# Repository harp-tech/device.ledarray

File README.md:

## Harp LED array

Controlling LED arrays that require more power. Ideally for opto-stimulation experiments.

### Key Features ###

* Controls up to 2 separate RGB LED
* Arrays and one common Infrared LED
* Two operation modes for each RGB LED Array: PWM or Interval

### Connectivity ###

* 1x clock sync input (CLKIN) [stereo jack]
* 1x USB (for computer) [USB type B]
* 1x flat cable
* 2x Digital Inputs (IN0, IN1) [flick lock male pins]
* 2x Digital Outputs (OUT0, OUT1) [flick lock male pins]
* 1x connector for 2 LED Arrays [10-pin flat-cable]

## Interface ##

The interface with the Harp board can be done through [Bonsai](https://bonsai-rx.org/) or a dedicated GUI (Graphical User Interface).

In order to use this GUI, there are some software that needs to be installed:

1 - Install the [drivers](https://bitbucket.org/fchampalimaud/downloads/downloads/UsbDriver-2.12.26.zip).

2 - Install the [runtime](https://bitbucket.org/fchampalimaud/downloads/downloads/Runtime-1.0.zip).

3 - Reboot the computer.

4 - Install the [GUI](https://bitbucket.org/fchampalimaud/downloads/downloads/Harp%20Led%20Array%20v2.2.0.zip).

## Licensing ##

Each subdirectory will contain a license or, possibly, a set of licenses if it involves both hardware and software.

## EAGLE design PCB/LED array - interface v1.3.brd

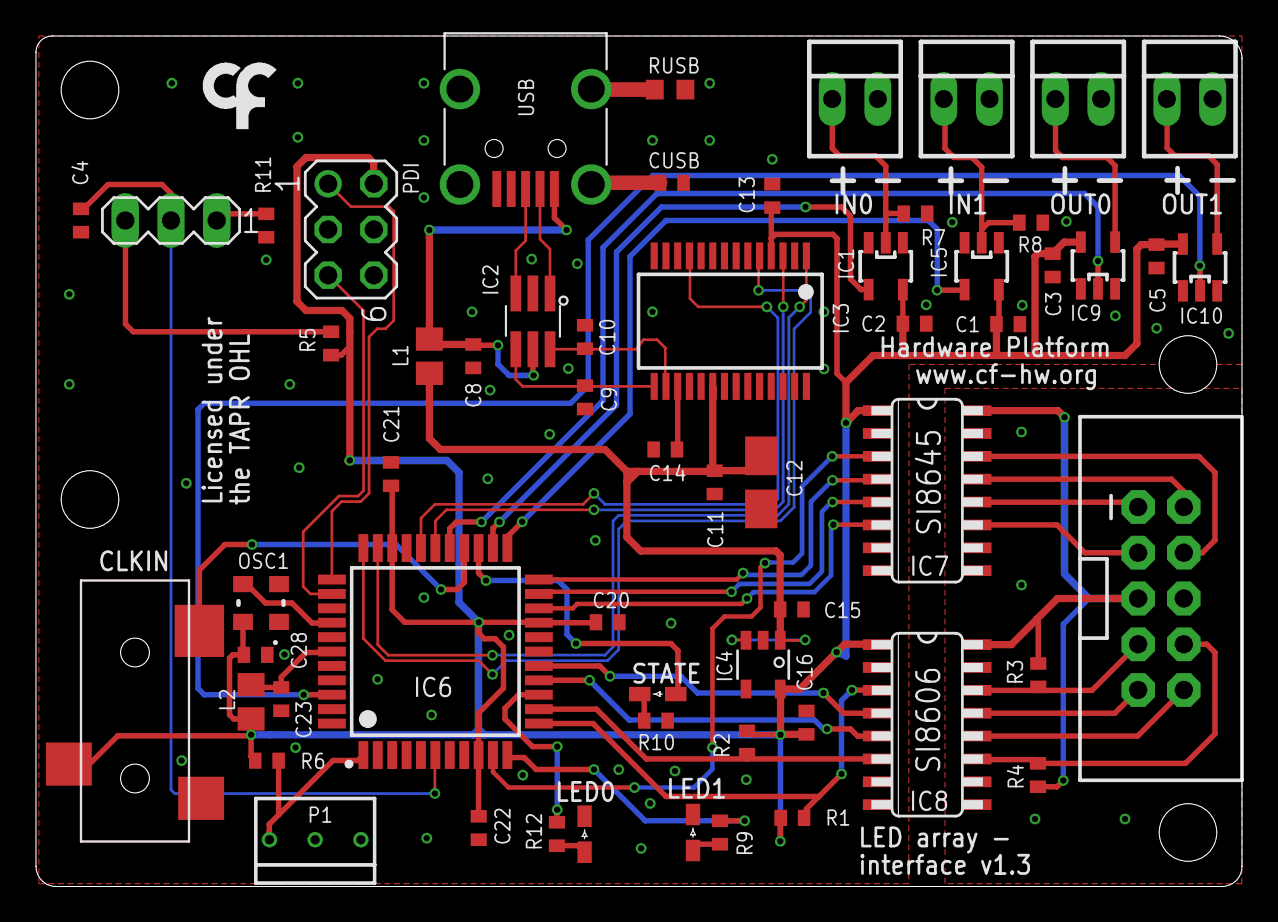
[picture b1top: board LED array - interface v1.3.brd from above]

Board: 2 copper layers, 67.0 x 47.2 mm, 61 parts (1 on the bottom side), 56 nets.

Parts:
C1, C2, C3, C5, C8, C11, C13, C14, C20, C21, C22, C28: 100nF; C0402
C4: 330nF NA; C0402
C9, C10: 47pF; C0402
C12: 4.7uF; A/3216-18W
C15, C16: 4.7uF; C0402
C23: 330nF; C0402
CLKIN: 35RASMT2BHNTRX
CUSB: 4.7nF; C0402
IC1, IC5, IC9, IC10: SN74LVC1G125; SOT23-5
IC2: USBLC6-2SC6; SOT23-6L
IC3: FT232RL; SSOP28
IC4: LP5907; TSOT23-5
IC6: ATXMEGAxxxA4U-AU; QFP80P1200X1200X120-44N
IC7: SI8645; NSOIC-16
IC8: SI8606; NSOIC-16
IN0, IN1: 22-23-2021
JP1: M05X2SHD; 2X5-SHROUDED
L1: ???; R0805
L2: 1u; R0805
LED0, LED1: GREEN; LED_HAND
OSC1: OSCILLATOR_3.2X2.5
OUT0, OUT1: 22-23-2021
P1: POT_BOURNS_3362M
PDI: MA03-2
R1, R2, R3, R4: 3k; R0402
R5, R11: 100k NA; R0402
R6: 1k 0.1%; R0402
R7, R8: 100k; R0402
R9, R10, R12: 68; R0402
RUSB: 1M; R0603
STATE: GREEN; LED_HAND
SV1: NA; MA03-1
U$1: LOGO_5
U$3: LOGO_7
USB: 240-0002-1

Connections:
ADC: IC6.1, P1.3, R6.1
ADC1: R5.1, SV1.3
AUX0: IC6.22, IC7.4
AUX1: IC6.21, IC7.5
AVCC: C23.1, IC6.39, L2.1
CLK: IC8.11, JP1.8, R4.1
CLK_SYNC: CLKIN.4, IC6.26
DAT: IC8.14, JP1.7, R3.1
DO2: IC7.13, JP1.2
DO3: IC7.12, JP1.1
FT_CTS: IC3.11, IC6.29
FT_RTS: IC3.3, IC6.28
FT_RXD: IC3.5, IC6.33
FT_TXD: IC3.1, IC6.32
GND: IC7.9, IC7.15, IC8.9, JP1.6
GND2: IC5.2, IN1.1, R8.2
GNDIO: C1.2, C2.2, C3.2, C4.2, C5.2, C8.2, C9.2, C10.2, C11.2, C12.-, C13.2, C14.2, C15.1, C16.1, C20.2, C21.2, C22.2, C23.2, C28.2, CLKIN.5, CUSB.2, IC1.1, IC1.3, IC2.P$2, IC3.7, IC3.18, IC3.21, IC3.25, IC3.26, IC4.2, IC5.1, IC5.3, IC6.8, IC6.18, IC6.30, IC6.38, IC6.40, IC6.43, IC7.2, IC7.8, IC8.8, IC9.1, IC9.3, IC10.1, IC10.3, IN0.2, IN1.2, LED0.K, LED1.K, OSC1.P$2, OUT0.2, OUT1.2, P1.1, P1.2, PDI.6, R7.1, R8.1, R10.1, R11.1, RUSB.2, USB.P$5
IN0: IC1.4, IC6.24
IN1: IC5.4, IC6.23
LED0: IC6.14, R12.2
LED0_PWR: IC6.15, IC8.5
LED0_TRANS: IC6.10, IC7.3
LED1: IC6.11, R9.2
LED1_PWR: IC6.16, IC8.4
LED1_TRANS: IC6.20, IC7.6
MODE0: C4.1, IC6.6, SV1.2
unnamed: R11.2, SV1.1
unnamed: C14.1, IC3.17
unnamed: IC9.4, OUT0.1
unnamed: IC2.P$3, USB.P$3
unnamed: LED0.A, R12.1
unnamed: IC10.4, OUT1.1
unnamed: R10.2, STATE.K
unnamed: IC1.2, IN0.1, R7.2
unnamed: LED1.A, R9.1
unnamed: C8.1, IC2.P$5, L1.2, USB.P$1
unnamed: IC2.P$1, USB.P$2
unnamed: CUSB.1, USB.SHIELD_4
unnamed: RUSB.1, USB.SHIELD_1
ON_IR: IC8.13, JP1.9
ON_LED: IC8.12, JP1.10
OSC1: IC6.37, OSC1.P$3
OUT0: IC6.27, IC9.2
OUT1: IC6.42, IC10.2
PDI-CLK: IC6.35, PDI.5
PDI-DATA: IC6.34, PDI.1
SCL: IC6.13, IC8.6, R2.1
SDA: IC6.12, IC8.3, R1.1
STATE_: IC6.25, STATE.A
TOG_IR: IC7.11, JP1.3
TOG_RED: IC7.14, JP1.4
USB5V: C11.1, C12.+, C15.2, IC3.20, IC4.1, IC4.3, L1.1
USBDM: C10.1, IC2.P$6, IC3.16
USBDP: C9.1, IC2.P$4, IC3.15
VCCIO: C1.1, C2.1, C3.1, C5.1, C13.1, C16.2, C20.1, C21.1, C22.1, C28.1, CLKIN.1, IC1.5, IC3.4, IC4.5, IC5.5, IC6.9, IC6.19, IC6.31, IC7.1, IC8.1, IC9.5, IC10.5, L2.2, OSC1.P$4, PDI.2, R1.2, R2.2, R5.2, R6.2
VDD: IC7.16, IC8.16, JP1.5, R3.2, R4.2

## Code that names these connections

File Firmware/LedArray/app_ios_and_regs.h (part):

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#define ADD_REG_POWER_EN                    32 // U8     Control the enable of both LEDs' supply
#define ADD_REG_LED_BEHAVING                33 // U8     Starts and stops the LED is behaving
#define ADD_REG_LED_ON                      34 // U8     Controls the on board's LED
#define ADD_REG_IN_STATE                    35 // U8     Reflects the state of both inputs
#define ADD_REG_OUT_CONFIGURATION           36 // U8     Configures which signal is connected to the digital outputs
#define ADD_REG_IN_CONFIGURATION            37 // U8     Configures the digital inputs
#define ADD_REG_LED_CONFIGURATION           38 // U8     Configures how LEDs will behave
#define ADD_REG_LED0_SUPPLY_PWR_CONF        39 // U8     Configuration of power to be aplied to LED0 [1;120]
#define ADD_REG_LED1_SUPPLY_PWR_CONF        40 // U8     Configuration of power to be aplied to LED1 [1;120]
#define ADD_REG_LED0_PWM_FREQ               41 // FLOAT  PWM frequency of LED0's power transistor [0.5;2000.0]
#define ADD_REG_LED0_PWM_DCYCLE             42 // FLOAT  PWM duty cycle of LED0's power transistor [0.1;99.9]
#define ADD_REG_LED0_PWM_PULSES             43 // U16    Number of PWM pulses (LED0) [1;65535]
#define ADD_REG_LED0_INTERVAL_ON            44 // U16    Time ON of LED0 (milliseconds) [1;65535]
#define ADD_REG_LED0_INTERVAL_OFF           45 // U16    Time OFF of LED0 (milliseconds) [1;65535]
#define ADD_REG_LED0_INTERVAL_PULSES        46 // U16    Number of pulses (LED0) [1;65535]
#define ADD_REG_LED0_INTERVAL_TAIL          47 // U16    Wait time between pulses (milliseconds) (LED0) [1;65535]
#define ADD_REG_LED0_INTERVAL_REPS          48 // U16    Number of repetitions of the entire scheme (LED0) [1;65535]
#define ADD_REG_LED1_PWM_FREQ               49 // FLOAT  PWM frequency of LED1's power transistor [0.5;2000.0]
#define ADD_REG_LED1_PWM_DCYCLE             50 // FLOAT  PWM duty cycle of LED1's power transistor [0.1;99.9]
#define ADD_REG_LED1_PWM_PULSES             51 // U16    Number of PWM pulses (LED1) [1;65535]
#define ADD_REG_LED1_INTERVAL_ON            52 // U16    Time ON of LED1 (milliseconds) [1;65535]
#define ADD_REG_LED1_INTERVAL_OFF           53 // U16    Time OFF of LED1 (milliseconds) [1;65535]
#define ADD_REG_LED1_INTERVAL_PULSES        54 // U16    Number of pulses (LED1) [1;65535]
#define ADD_REG_LED1_INTERVAL_TAIL          55 // U16    Wait time between pulses (milliseconds) (LED1) [1;65535]
#define ADD_REG_LED1_INTERVAL_REPS          56 // U16    Number of repetitions of the entire scheme (LED1) [1;65535]
#define ADD_REG_LED0_PWM_FREQ_REAL          57 // FLOAT  Real PWM frequency of LED0's power transistor
#define ADD_REG_LED0_PWM_DCYCLE_REAL        58 // FLOAT  Real PWM duty cycle of LED0's power transistor
#define ADD_REG_LED1_PWM_FREQ_REAL          59 // FLOAT  Real PWM frequency of LED1's power transistor
#define ADD_REG_LED1_PWM_DCYCLE_REAL        60 // FLOAT  Real PWM duty cycle of LED1's power transistor
#define ADD_REG_AUX_DIG_OUT                 61 // U8     Controls the auxiliar digital output
#define ADD_REG_AUX_SUPPLY_PWR_CONF         62 // U8     Configuration of power to be aplied to auxiliar LED [1;120]
#define ADD_REG_OUT_STATE                   63 // U8     Digital output control
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/************************************************************************/
/* Registers' bits                                                      */
/************************************************************************/
#define B_LED0_PWR_EN                      (1<<0)       // Enable LED0 supply when equal to 1
#define B_LED1_PWR_EN                      (1<<1)       // Enable LED1 supply when equal to 1
#define B_LED0_PWR_DIS                     (1<<2)       // Disable LED0 supply when equal to 1
#define B_LED1_PWR_DIS                     (1<<3)       // Disable LED1 supply when equal to 1
#define B_LED0_START                       (1<<0)       // Start configured behaviour on LED0 when equal to 1
#define B_LED1_START                       (1<<1)       // Start configured behaviour on LED1 when equal to 1
#define B_LED0_STOP                        (1<<2)       // Stop configured behaviour on LED0 when equal to 1
#define B_LED1_STOP                        (1<<3)       // Stop configured behaviour on LED1 when equal to 1
#define B_LED0_TO_ON                       (1<<0)       // Turn LED0 on if equal to 1
#define B_LED1_TO_ON                       (1<<1)       // Turn LED1 on if equal to 1
#define B_LED0_TO_OFF                      (1<<2)       // Turn LED0 off if equal to 1
#define B_LED1_TO_OFF                      (1<<3)       // Turn LED1 off if equal to 1
#define B_IN0                              (1<<0)       // State of input IN0
#define B_IN1                              (1<<1)       // State of input IN1
#define MSK_OUT0_CONF                      (3<<0)       // Select OUT0 function
#define GM_OUT0_SOFTWARE                   (0<<0)       // Pure digital output
#define GM_OUT0_LED0_PWR_EN                (1<<0)       // Equal to bit LED0_PWR_EN
#define GM_OUT0_LED0_START                 (2<<0)       // Equal to bit LED0_START
#define GM_OUT0_LED0_ON                    (3<<0)       // Equal to bit LED0_ON
#define MSK_OUT1_CONF                      (3<<4)       // Select OUT1 function
#define GM_OUT1_SOFTWARE                   (0<<4)       // Pure digital output
#define GM_OUT1_LED1_PWR_EN                (1<<4)       // Equal to bit LED1_PWR_EN
#define GM_OUT1_LED1_START                 (2<<4)       // Equal to bit LED1_START
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#define GM_IN1_CONF_LED1_START             (4<<4)       // IN1 controls bit LED1_START
#define GM_IN1_CONF_LED1_ON                (5<<4)       // IN1 controls bit LED1_ON
#define GM_IN1_CONF_NOT                    (6<<4)       // IN1 Controls nothing
#define MSK_LED0_CONF                      (3<<0)       // Configure LED0
#define MSK_LED1_CONF                      (3<<4)       // Configure LED1
#define GM_LED0_PWM                        (0<<0)       // LED0 uses configured PWM
#define GM_LED0_INTERVAL                   (1<<0)       // LED0 uses configured intervals
#define GM_LED1_PWM                        (0<<4)       // LED1 uses configured PWM
#define GM_LED1_INTERVAL                   (1<<4)       // LED1 uses configured intervals
#define B_AUX0_TO_HIGH                     (1<<0)       // Turn AUX0 to high level if equal to 1
#define B_AUX1_TO_HIGH                     (1<<1)       // Turn AUX1 to high level if equal to 1
#define B_AUX0_TO_LOW                      (1<<2)       // Turn AUX0 to low level if equal to 1
#define B_AUX1_TO_LOW                      (1<<3)       // Turn AUX1 to low level if equal to 1
#define B_OUT0_TO_HIGH                     (1<<0)       // Turn OUT0 to high level if equal to 1
#define B_OUT1_TO_HIGH                     (1<<1)       // Turn OUT1 to high level if equal to 1
#define B_OUT0_TO_LOW                      (1<<2)       // Turn OUT0 to low level if equal to 1
#define B_OUT1_TO_LOW                      (1<<3)       // Turn OUT1 to low level if equal to 1
#define B_EVT_LED_ON                       (1<<0)       // Event of register LED_ON
#define B_EVT_IN_STATE                     (1<<1)       // Event of register IN_STATE

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
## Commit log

2018-10-26 Added the firmware files.
2018-10-26 Added .gitignore.
2018-10-30 Added new registers and renamed some digital lines.
2018-10-30 Fixed issue that happens when writing the intensity to the auxiliary array.
2019-05-09 Implemented control of the digtal outputs.
2019-05-09 Raised firmware to version 2.2.
2019-08-09 Ability to turn LED's transistor off when stop the behavior. Increased version to fw 2.3.
2020-02-26 Added the functions to control the fly pit boxes.
2020-02-26 Implemented fly pit boxes control and added ability to program DC/DCs with user defaults after boot. Increased fw version to 2.4.
2022-12-20 Add PCB and BOM files
2022-12-20 Add licenses and readme
2022-12-23 refactor repository structure
2023-07-05 update pcb asset image
2023-07-06 resize pcb image
2023-07-06 add automatic interface generation files
2023-07-19 update .yml - naming
2023-07-19 update .yml - minor naming changes
2023-07-24 update device.yml with new LED modes naming
2023-07-24 Add schema proposal
2023-07-25 Modify register description
2023-07-26 remove .txt extensions
2023-07-26 Rename firmware license file
2023-07-26 Align .gitignore to other device repositories
2023-07-26 Regenerate device classes
2023-07-26 Increment preview release
2023-07-31 Update interface to use new generators
2023-08-03 Add missing package metadata for stable release
2023-08-10 Add gitignore to Hardware
2023-08-23 Update .cppproj library path
2024-11-13 Update device schema source
2024-11-13 Update package metadata, version and add library package
2024-11-13 Update generators and regenerate interface
2025-02-11 update fw version and remove secondary bus validation
2025-02-21 Update fw to 2.6 and revert smbus init
2025-02-25 Update fw version and remove smbus init
2025-10-28 Updated to atxmega core 1.15

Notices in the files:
PCB/LED array - interface v1.3.brd:
Licensed under the TAPR Open
Hardware License (www.tapr.org/OHL)
Copyright 2016-2018 Artur Silva and Filipe Carvalho
parts and their libraries:
SparkFun-Connectors: Licensing: Creative Commons ShareAlike 4.0 International - https://creativecommons.org/licenses/by-sa/4.0
